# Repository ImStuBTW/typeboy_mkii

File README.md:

# The TypeBoy Mk II

The Mark II is an updated design to the original TypeBoy keyboard. It continues to leverage the "TypePak" cartridge to house the keyboard's microcontroller and other support circuitry. This revision of the TypeBoy uses a more traditional ortholinear keyboard layout, and replaces the previous 3D printed design with a PCB sandwich approach. For more information on the keyboard's background, please feel free to check out this companying blog post.

## Primary Features

* TypeBoy Cartridge Support (Integrated XAIO BLE, LiPo Battery, Shift Register, and Sharp Memory Display)
* 6x4+5 ortholinear layout with a staggered modifier row and enlarged space keys.
* Choc v1 switches with Choc spacing.
* SIQ-02FVS3 thumb wheel encoders (with pushbutton support).
* PCB sandwich design.
* ZMK support.

## Ergogen Outputs

The TypeBoy Mk II was designed once again using the [Ergogen](https://github.com/ergogen/ergogen) keyboard layout generator. In this instance, Ergogen was used to create the PCB outputs for the top, middle, and bottom layers of the keyboard. The silkscreen designs were created in Figma and imported directly into the KiCAD outputs. The final routing for the middle layer was also performed in KiCAD.

## Additional Footprints

Ergogen v4 supports custom footprints! The TypeBoy colors outsides the lines and includes a few not included in the standard repo:

* buttonrightangle.js - A right angle pushbutton.
* gbareversible.js - A reversible game boy cartridge slot footprint based off of [Martin Refseth's KiCAD footprint](https://github.com/HDR/Game-Boy-KiCad-Library/blob/master/Footprints/DSL_Cartridge_Reader.kicad_mod).
* lowproro.js - A footprint for the SIQ-02FVS3 low profile rotary encoder. Used in an earlier TypeBoy design.
* mountinghole_m3.js - An M3 mounting hole footprint.
* spdt.js - A right angle power switch.

## Build of Materials

| Part                             | Amount         | Price       | Link |
| -------------------------------- | -------------- | ----------- | ---- |
| TypePak Cartridges               | 2              | $20         | https://github.com/ImStuBTW/typeboy_and_typepak/tree/main/typepak |
| TypeBoy Mk II PCBs Via JLCPCB    | 3 (5 PCB Packs) | $45.00 USD (Incl. Shipping) | https://jlcpcb.com |
| Game Boy Cartridge Slot          | 2              | $5.00 USD  | https://www.aliexpress.us/item/2255800103876564.html |
| SIQ-02FVS3 Thumb Wheel           | 2              | $6.00 USD   | https://www.aliexpress.us/item/3256804405904721.html |
| Right Angle Pushbutton           | 2              | $1.00 USD   | https://www.mouser.com/ProductDetail/642-MJTP1117 |
| Right Angle Switch               | 2              | $1.50 USD   | https://www.mouser.com/ProductDetail/612-EG1213 |
| Choc Hotswap Sockets             | 58             | $12.00 USD  | https://www.aliexpress.us/item/3256803687338432.html |
| 1N4148 T4 Diodes                 | 58             | $3.00 USD   | https://www.aliexpress.us/item/2255800498728983.html |
| Choc Switches                    | 58             | $28.00 USD  | https://www.aliexpress.us/item/3256805260407528.html |
| Choc Keycaps                     | Alphas + Mods  | $~60.00 USD | https://mkultra.click/mbk-legend-keycaps/ |
| 12mm M3 Screws                   | 18             | $2.00 USD   | https://www.aliexpress.us/item/3256803547633472.html |
| M3 Washers                       | 54             | $10.00 USD  | https://www.aliexpress.us/item/3256804700714045.html |
| M3 Nuts                          | 18             | $5.00 USD   | https://www.aliexpress.us/item/2255800148575548.html |
| Bumpons                          | 1 Pack         | $10.00 USD | https://www.amazon.com/Adhesive-Bumper-106-PC-Spherical-Square/dp/B06XPCLN23/ |

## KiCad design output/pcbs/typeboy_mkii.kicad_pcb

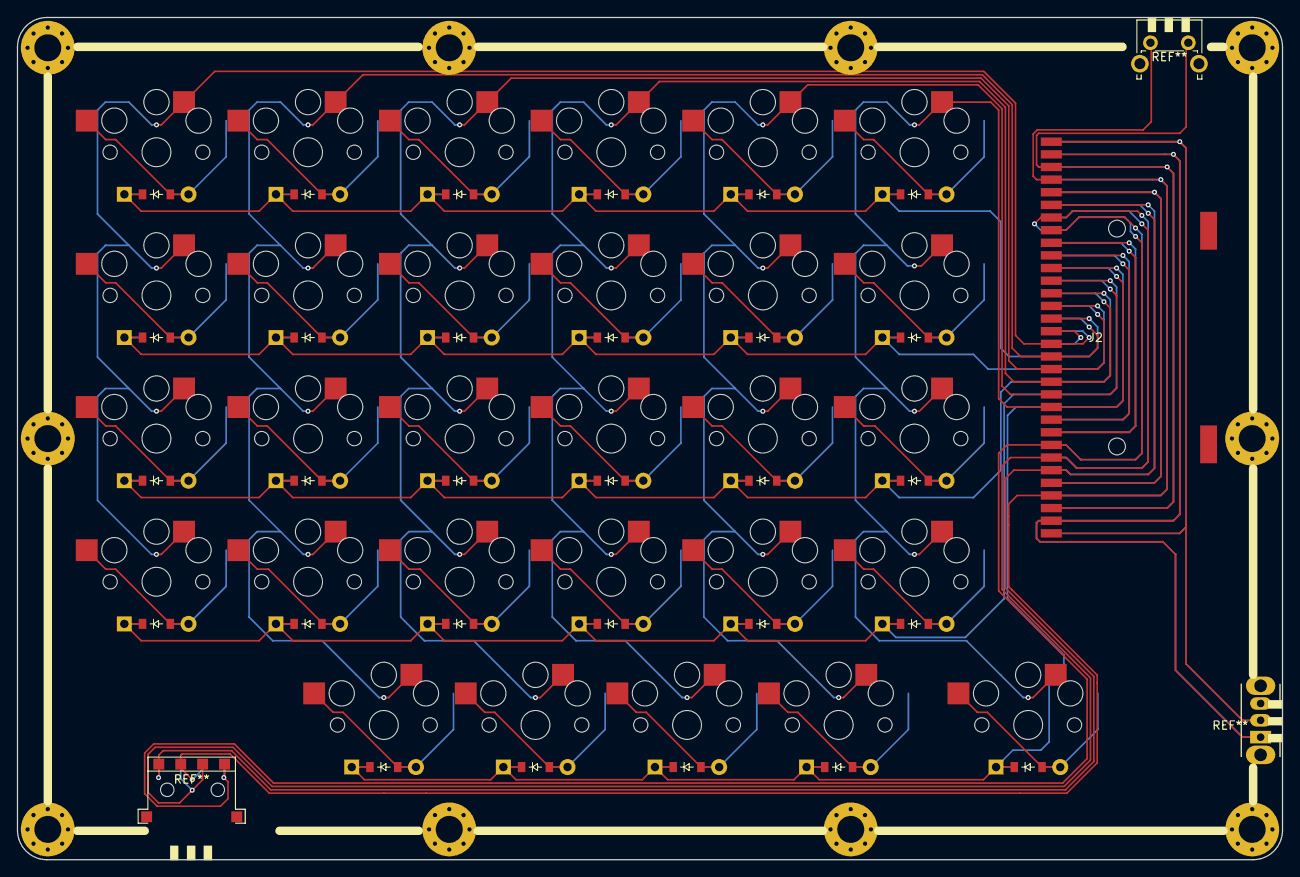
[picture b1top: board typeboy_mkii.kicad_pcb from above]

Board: 2 copper layers, 150.2 x 100.0 mm, 59 parts (0 on the bottom side), 55 nets.

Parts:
D1, D2, D3, D4, D5, D6, D7, D8, D9, D10, D11, D12, D13, D14, D15, D16, D17, D18, D19, D20, D21, D22, D23, D24, D25, D26, D27, D28, D29: ComboDiode
J2: CartBus; GBA_Reversible_Cart_Reader
S1, S2, S3, S4, S5, S6, S7, S8, S9, S10, S11, S12, S13, S14, S15, S16, S17, S18, S19, S20, S21, S22, S23, S24, S25, S26, S27, S28, S29: PG1350

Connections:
BATIN: J2.2, J2.31, J2.34, J2.63
BATOUT: J2.1, J2.32, J2.33, J2.64
GND: J2.4, J2.29, J2.36, J2.61
IO_CS: J2.9, J2.56
LCD_CS: J2.16, J2.49
MISO: J2.7, J2.25, J2.40, J2.58
MOSI: J2.6, J2.59
NFC0: J2.26, J2.39
NFC1: J2.27, J2.38
RST: J2.3, J2.30, J2.35, J2.62
SCK: J2.8, J2.57
VCC: J2.5, J2.28, J2.37, J2.60
col0: J2.17, J2.48, S1.1, S2.1, S3.1, S4.1
col1: J2.18, J2.47, S5.1, S6.1, S7.1, S8.1, S9.1
col2: J2.19, J2.46, S10.1, S11.1, S12.1, S13.1, S14.1
col3: J2.20, J2.45, S15.1, S16.1, S17.1, S18.1, S19.1
col4: J2.21, J2.44, S20.1, S21.1, S22.1, S23.1, S24.1
col5: J2.22, J2.43, S25.1, S26.1, S27.1, S28.1, S29.1
col6: J2.23, J2.42
col7: J2.24, J2.41
index_bottom: D21.2, S21.2
index_home: D22.2, S22.2
index_mod: D20.2, S20.2
index_num: D24.2, S24.2
index_top: D23.2, S23.2
inner_bottom: D26.2, S26.2
inner_home: D27.2, S27.2
inner_mod: D25.2, S25.2
inner_num: D29.2, S29.2
inner_top: D28.2, S28.2
middle_bottom: D16.2, S16.2
middle_home: D17.2, S17.2
middle_mod: D15.2, S15.2
middle_num: D19.2, S19.2
middle_top: D18.2, S18.2
outer_bottom: D1.2, S1.2
outer_home: D2.2, S2.2
outer_num: D4.2, S4.2
outer_top: D3.2, S3.2
pinky_bottom: D6.2, S6.2
pinky_home: D7.2, S7.2
pinky_mod: D5.2, S5.2
pinky_num: D9.2, S9.2
pinky_top: D8.2, S8.2
ring_bottom: D11.2, S11.2
ring_home: D12.2, S12.2
ring_mod: D10.2, S10.2
ring_num: D14.2, S14.2
ring_top: D13.2, S13.2
row0: D4.1, D9.1, D14.1, D19.1, D24.1, D29.1, J2.15, J2.50
row1: D3.1, D8.1, D13.1, D18.1, D23.1, D28.1, J2.14, J2.51
row2: D2.1, D7.1, D12.1, D17.1, D22.1, D27.1, J2.13, J2.52
row3: D1.1, D6.1, D11.1, D16.1, D21.1, D26.1, J2.12, J2.53
row4: D5.1, D10.1, D15.1, D20.1, D25.1, J2.11, J2.54
row5: J2.10, J2.55

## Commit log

2024-01-26 Added .gitignore
2024-01-26 Fixed Images
2024-01-26 Fixed Image References.
2024-01-28 Fixed typos.
